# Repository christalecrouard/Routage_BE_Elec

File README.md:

# Routage_BE_Elec
Projet de 3IMACS AE de routage d'une carte électronique sur KiCad

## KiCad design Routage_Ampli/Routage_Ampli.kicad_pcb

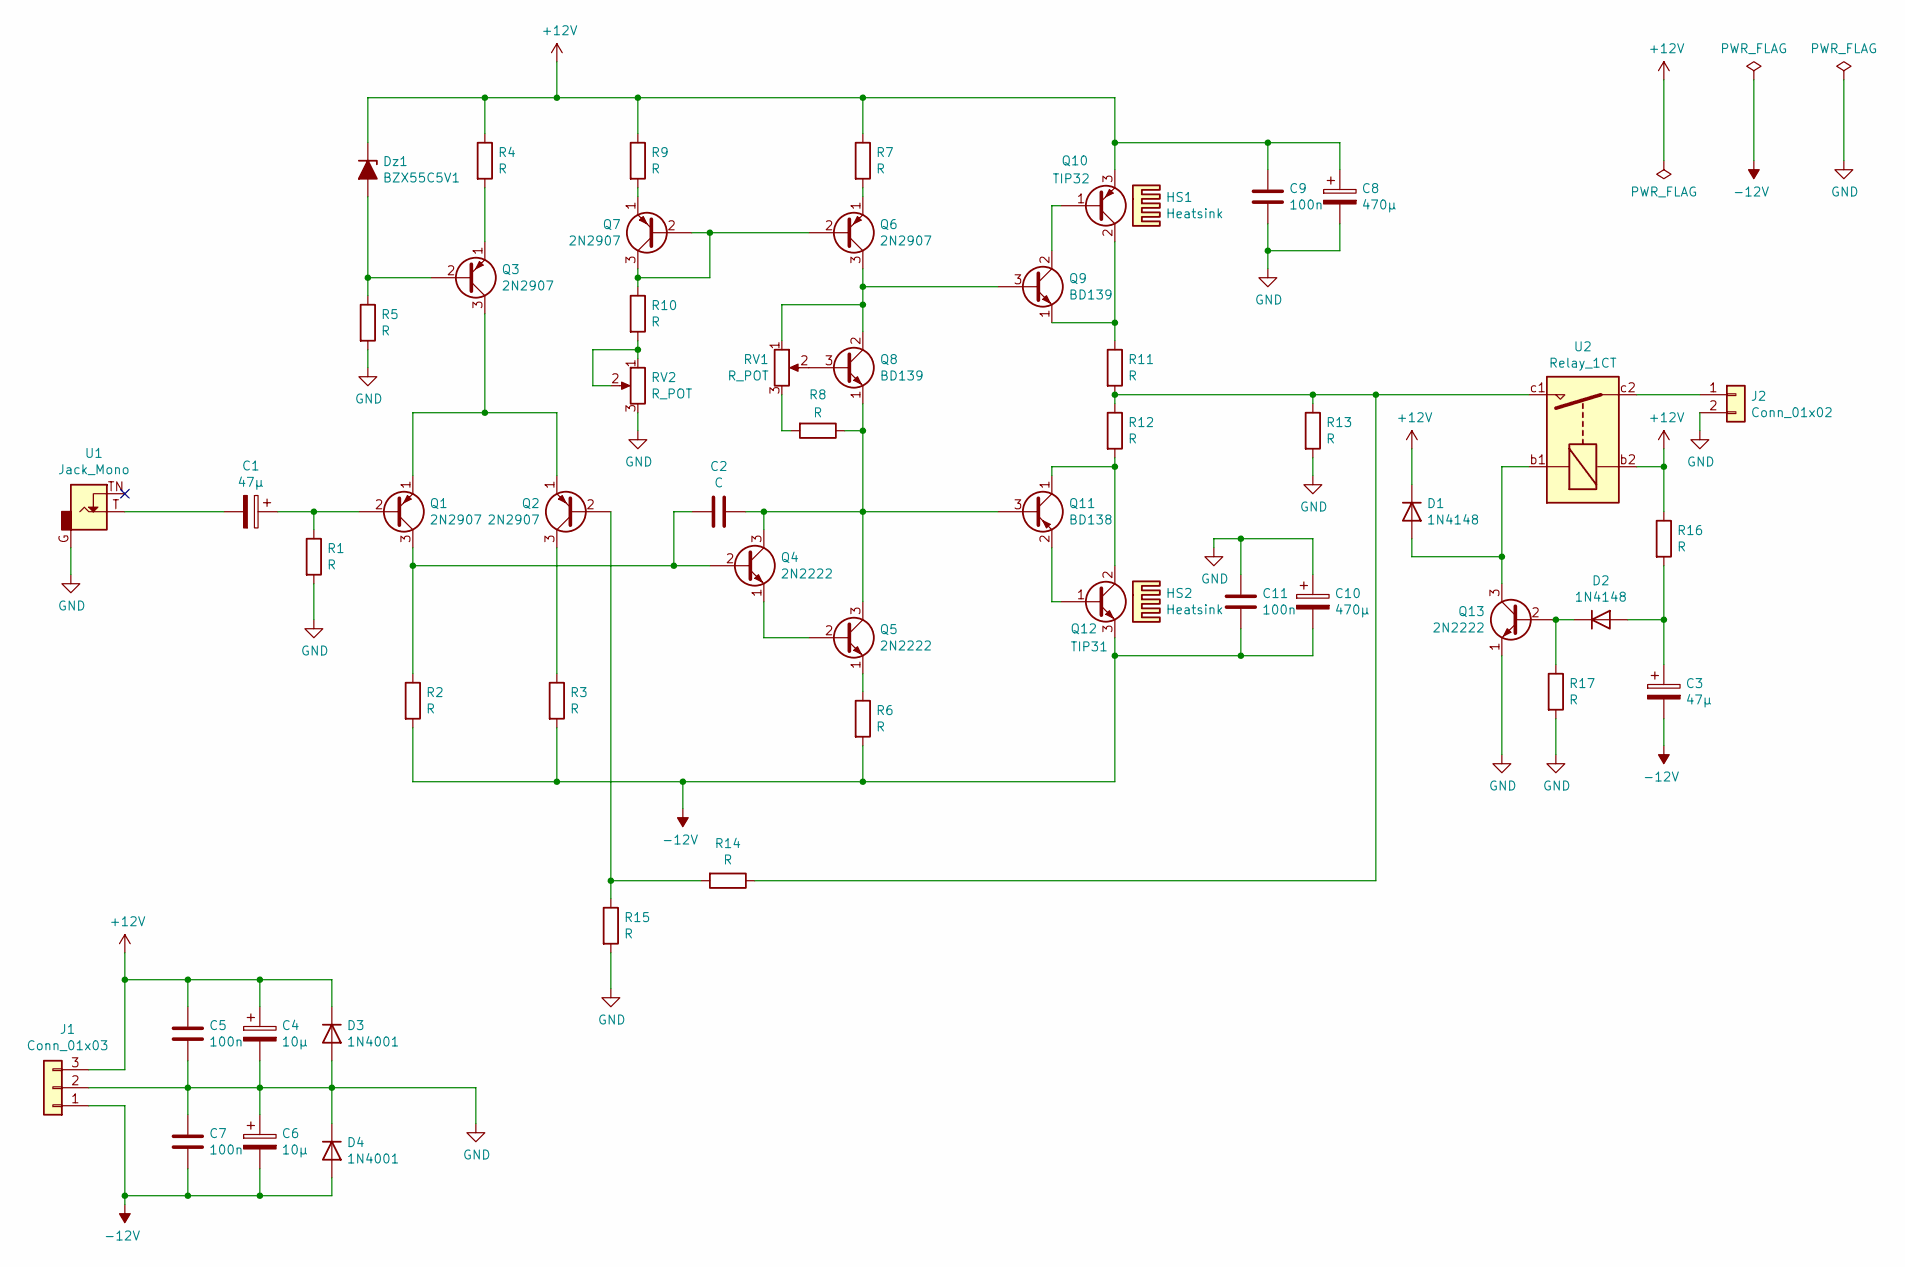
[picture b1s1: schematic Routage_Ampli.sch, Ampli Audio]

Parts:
C1, C3: 47µ; CP_Radial_D8.0mm_P5.00mm
C2: C; C_Rect_L7.2mm_W3.5mm_P5.00mm_FKS2_FKP2_MKS2_MKP2
C4, C6: 10µ; CP_Radial_D8.0mm_P5.00mm
C5, C7, C9, C11: 100n; C_Rect_L7.2mm_W3.5mm_P5.00mm_FKS2_FKP2_MKS2_MKP2
C8, C10: 470µ; CP_Radial_D12.5mm_P5.00mm
D1, D2: 1N4148; D_DO-35_SOD27_P10.16mm_Horizontal
D3, D4: 1N4001; D_DO-35_SOD27_P10.16mm_Horizontal
Dz1: BZX55C5V1; D_DO-35_SOD27_P10.16mm_Horizontal
HS1, HS2: Heatsink; Heatsink_Fischer_SK104-STC-STIC_35x13mm_2xDrill2.5mm
J1: Conn_01x03; PhoenixContact_MSTBVA_2,5_3-G-5,08_1x03_P5.08mm_Vertical
J2: Conn_01x02; PhoenixContact_MSTBVA_2,5_2-G-5,08_1x02_P5.08mm_Vertical
Q1, Q2, Q3, Q6, Q7: 2N2907; TO-18-3
Q4, Q5, Q13: 2N2222; TO-18-3
Q8, Q9: BD139; TO-126-3_Vertical
Q10: TIP32; TO-220-3_Vertical
Q11: BD138; TO-126-3_Vertical
Q12: TIP31; TO-220-3_Vertical
R1, R2, R3, R4, R5, R6, R7, R8, R9, R10, R13, R14, R15, R16, R17: R; R_Axial_DIN0207_L6.3mm_D2.5mm_P10.16mm_Horizontal
R11, R12: R; R_Axial_DIN0516_L15.5mm_D5.0mm_P20.32mm_Horizontal
RV1, RV2: R_POT; Potentiometer_Bourns_3296W_Vertical
U1: Jack_Mono; Jack_35RAPC2AV
U2: Relay_1CT; Relay_CT

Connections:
+12V: C4.1, C5.1, C8.1, C9.1, D1.1 (K), D3.1 (K), Dz1.1 (K), J1.3, Q10.3 (E), R4.1, R7.1, R9.1, R16.1, U2.b2
-12V: C3.2, C6.2, C7.2, C10.2, C11.2, D4.2 (A), J1.1, Q12.3 (E), R2.2, R3.2, R6.2
GND: C4.2, C5.2, C6.1, C7.1, C8.2, C9.2, C10.1, C11.1, D3.2 (A), D4.1 (K), J1.2, J2.2, Q13.1 (E), R1.2, R5.2, R13.2, R15.2, R17.2, RV2.3, U1.G
unnamed: C1.1, Q1.2 (B), R1.1
unnamed: C1.2, U1.T
unnamed: C2.1, Q4.3 (C), Q5.3 (C), Q8.1 (E), Q11.3 (B), R8.1
unnamed: C2.2, Q1.3 (C), Q4.2 (B), R2.1
unnamed: C3.1, D2.2 (A), R16.2
unnamed: D1.2 (A), Q13.3 (C), U2.b1
unnamed: D2.1 (K), Q13.2 (B), R17.1
unnamed: Dz1.2 (A), Q3.2 (B), R5.1
unnamed: J2.1, U2.c2
unnamed: Q1.1 (E), Q2.1 (E), Q3.3 (C)
unnamed: Q2.2 (B), R14.2, R15.1
unnamed: Q2.3 (C), R3.1
unnamed: Q3.1 (E), R4.2
unnamed: Q4.1 (E), Q5.2 (B)
unnamed: Q5.1 (E), R6.1
unnamed: Q6.1 (E), R7.2
unnamed: Q6.2 (B), Q7.2 (B), Q7.3 (C), R10.1
unnamed: Q6.3 (C), Q8.2 (C), Q9.3 (B), RV1.1
unnamed: Q7.1 (E), R9.2
unnamed: Q8.3 (B), RV1.2
unnamed: Q9.2 (C), Q10.1 (B)
unnamed: Q9.1 (E), Q10.2 (C), R11.1
unnamed: Q11.1 (C), Q12.2 (C), R12.2
unnamed: Q11.2 (E), Q12.1 (B)
unnamed: R8.2, RV1.3
unnamed: R10.2, RV2.1, RV2.2
unnamed: R11.2, R12.1, R13.1, R14.1, U2.c1

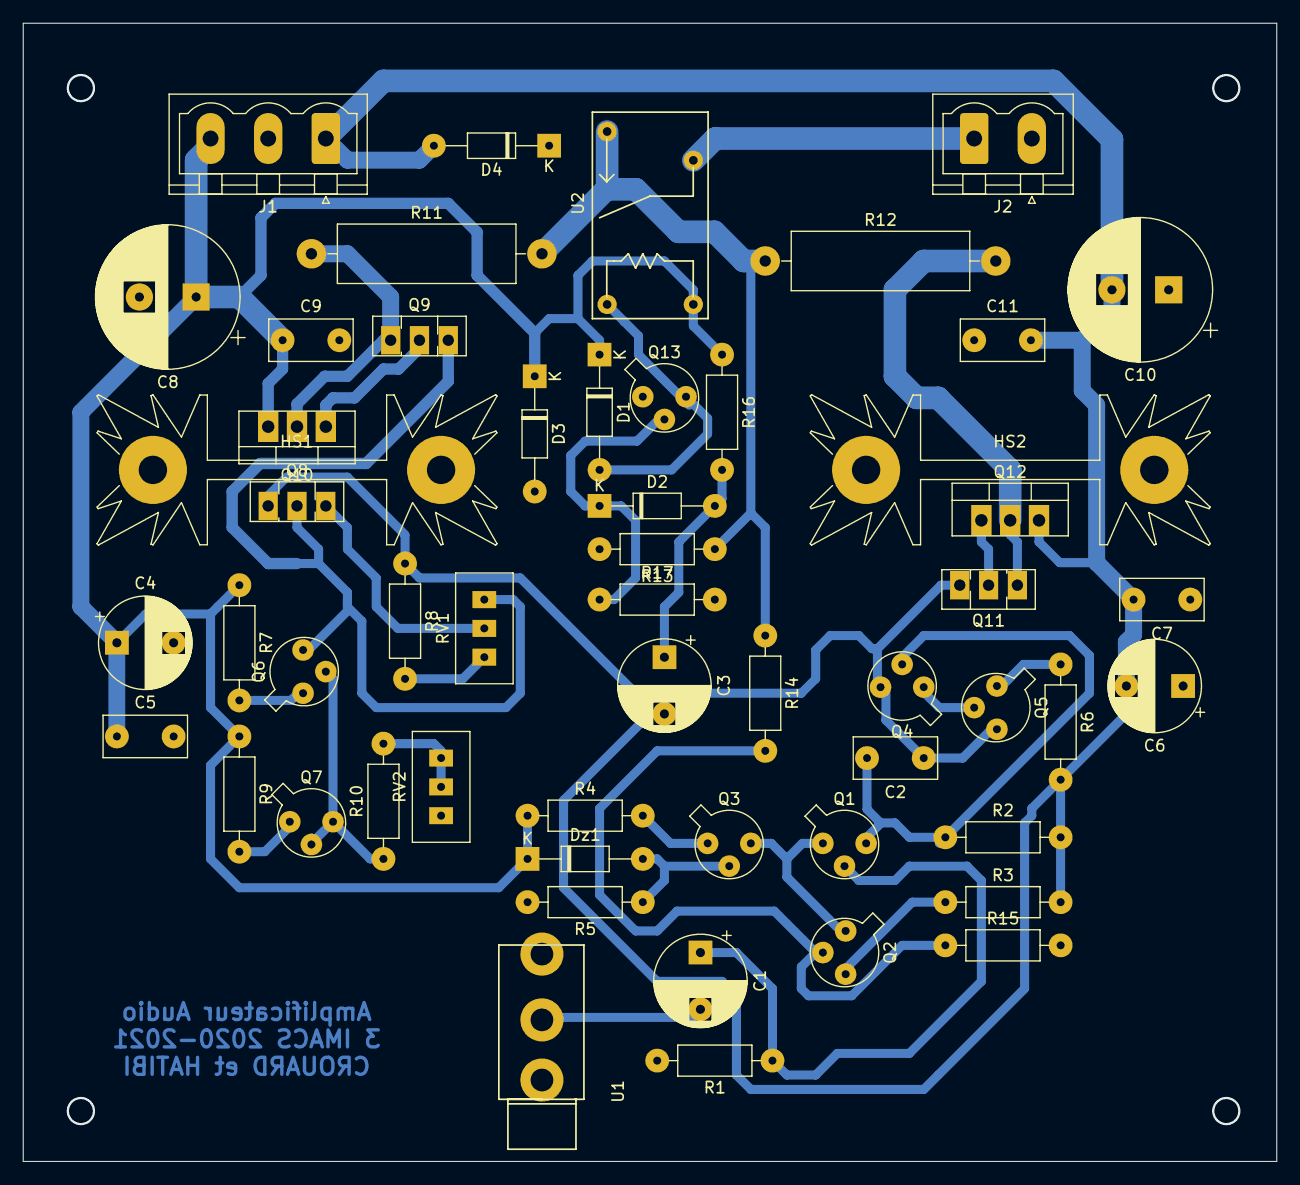
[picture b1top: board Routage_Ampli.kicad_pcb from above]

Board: 2 copper layers, 110.5 x 100.3 mm, 54 parts (0 on the bottom side), 30 nets.

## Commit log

2021-03-16 Initialisation du projet - Etapes 1 à 5
    Réalisation du schematic, création des composants manquants (Relay, Jack) symboles et empreintes. Initialisation du Circuit avec les cotes, les connecteurs et les pads.
2021-03-18 Début Placement + Routage
2021-03-18 routage_v1
2021-03-24 Ajout PDF Placement
    Upload du pdf du placemnt en version N&B pour correction
2021-03-31 Version avant correction
2021-04-09 Version pour correction : J-7
    Le plan de masse n'a pas été réalisé. On a routé les GND ensemble plutôt. On attend le Go de Mr Rocacher pour le faire.
    Le DRC fonctionne mais pas sûrs que les largeurs soient bonnes ni qu'il y ait des fils trop longs.
2021-04-10 Version finale
    Ajout u plan de masse et corrections des dernières erreurs. Sans straps en simple face. GG !
2021-04-11 Derniers détails
    Ajout de derniers détails : Texte en bottom, diodes de protection, mise à jour de la lib
